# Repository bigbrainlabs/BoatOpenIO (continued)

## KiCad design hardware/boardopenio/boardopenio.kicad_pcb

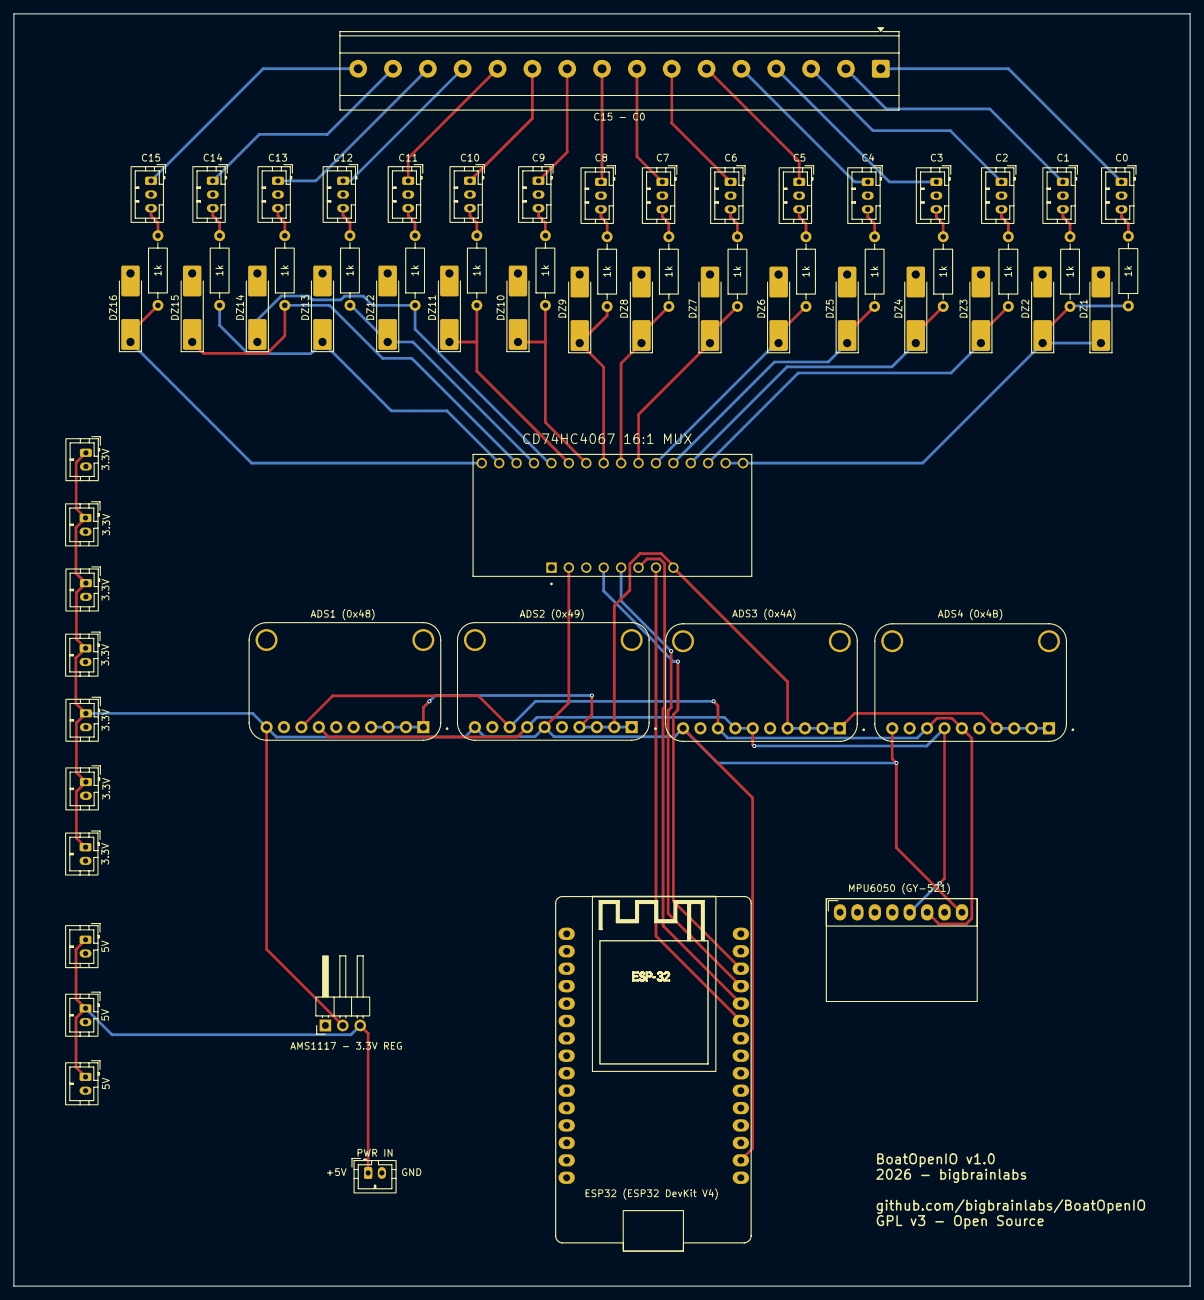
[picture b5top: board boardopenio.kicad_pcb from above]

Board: 2 copper layers, 171.5 x 185.5 mm, 68 parts (0 on the bottom side), 57 nets.

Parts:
3.3V, 3.3V#2, 3.3V#3, 3.3V#4, 3.3V#5, 3.3V#6, 3.3V#7, 5V, 5V#2, 5V#3: Conn_01x02; JST_PH_B2B-PH-K_1x02_P2.00mm_Vertical
ADS1 (0x48), ADS2 (0x49), ADS3 (0x4A), ADS4 (0x4B): ZC261500; MODULE_ZC261500
AMS1117 - 3.3V REG: AMS1117CD-3.3; PinHeader_1x03_P2.54mm_Horizontal
C0, C1, C2, C3, C4, C5, C6, C7, C8, C9, C10, C11, C12, C13, C14, C15: Conn_01x03_Pin; JST_PH_B3B-PH-K_1x03_P2.00mm_Vertical
C15 - C0: Screw_Terminal_01x16; TerminalBlock_Phoenix_MKDS-3-16-5.08_1x16_P5.08mm_Horizontal
CD74HC4067 16:1 MUX: CD74HC4067 MUX; MODULE_BOB-09056
DZ1, DZ2, DZ3, DZ4, DZ5, DZ6, DZ7, DZ8, DZ9, DZ10, DZ11, DZ12, DZ13, DZ14, DZ15, DZ16: Zener 3v3; D_MELF-RM10_Universal_Handsoldering
ESP32 (ESP32 DevKit V4): DOIT_ESP32_DEVKIT_30Pins
MPU6050 (GY-521): MPU6050; MPU6050_Breakout
PWR IN: Conn_01x02; JST_PH_B2B-PH-K_1x02_P2.00mm_Vertical
R1, R2, R3, R4, R5, R6, R7, R8, R9, R10, R11, R12, R13, R14, R15, R16: 1k; R_Axial_DIN0207_L6.3mm_D2.5mm_P10.16mm_Horizontal

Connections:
GND: 3.3V.2, 3.3V#2.2, 3.3V#3.2, 3.3V#4.2, 3.3V#5.2, 3.3V#6.2, 3.3V#7.2, 5V.2, 5V#2.2, 5V#3.2, ADS1 (0x48).6 (ADDR), ADS1 (0x48).9 (GND), ADS2 (0x49).9 (GND), ADS3 (0x4A).9 (GND), ADS4 (0x4B).9 (GND), AMS1117 - 3.3V REG.1 (GND), C0.2, C1.2, C2.2, C3.2, C4.2, C5.2, C6.2, C7.2, C8.2, C9.2, C10.2, C11.2, C12.2, C13.2, C14.2, C15.2, CD74HC4067 16:1 MUX.JP3-1 (GND), CD74HC4067 16:1 MUX.JP3-3 (EN), DZ1.2 (A), DZ2.2 (A), DZ3.2 (A), DZ4.2 (A), DZ5.2 (A), DZ6.2 (A), DZ7.2 (A), DZ8.2 (A), DZ9.2 (A), DZ10.2 (A), DZ11.2 (A), DZ12.2 (A), DZ13.2 (A), DZ14.2 (A), DZ15.2 (A), DZ16.2 (A), ESP32 (ESP32 DevKit V4).1 (GND), ESP32 (ESP32 DevKit V4).15 (GND), MPU6050 (GY-521).7 (GND), PWR IN.2
unnamed: CD74HC4067 16:1 MUX.JP1-15 (C14), CD74HC4067 16:1 MUX.JP1-16 (C15), DZ1.1 (K), DZ2.1 (K), R1.1, R2.1
unnamed: CD74HC4067 16:1 MUX.JP1-14 (C13), DZ3.1 (K), R3.1
unnamed: CD74HC4067 16:1 MUX.JP1-13 (C12), DZ4.1 (K), R4.1
unnamed: CD74HC4067 16:1 MUX.JP1-12 (C11), DZ5.1 (K), R5.1
unnamed: CD74HC4067 16:1 MUX.JP1-11 (C10), DZ6.1 (K), R6.1
unnamed: CD74HC4067 16:1 MUX.JP1-10 (C9), DZ7.1 (K), R7.1
unnamed: CD74HC4067 16:1 MUX.JP1-9 (C8), DZ8.1 (K), R8.1
unnamed: CD74HC4067 16:1 MUX.JP1-8 (C7), DZ9.1 (K), R9.1
unnamed: CD74HC4067 16:1 MUX.JP1-7 (C6), DZ10.1 (K), R10.1
unnamed: CD74HC4067 16:1 MUX.JP1-6 (C5), DZ11.1 (K), R11.1
unnamed: CD74HC4067 16:1 MUX.JP1-4 (C3), DZ12.1 (K), R13.1
unnamed: CD74HC4067 16:1 MUX.JP1-2 (C1), DZ13.1 (K), R15.1
unnamed: CD74HC4067 16:1 MUX.JP1-5 (C4), DZ14.1 (K), R12.1
unnamed: CD74HC4067 16:1 MUX.JP1-3 (C2), DZ15.1 (K), R14.1
unnamed: CD74HC4067 16:1 MUX.JP1-1 (C0), DZ16.1 (K), R16.1
unnamed: C0.1, C15 - C0.1
unnamed: C0.3, R1.2
unnamed: C1.1, C15 - C0.2
unnamed: C1.3, R2.2
unnamed: C2.3, R3.2
unnamed: C3.3, R4.2
unnamed: C4.3, R5.2
unnamed: C5.3, R6.2
unnamed: C6.3, R7.2
unnamed: C7.3, R8.2
unnamed: C8.3, R9.2
unnamed: C9.1, C15 - C0.10
unnamed: C9.3, R10.2
unnamed: C10.1, C15 - C0.11
unnamed: C10.3, R11.2
unnamed: C11.1, C15 - C0.12
unnamed: C11.3, R12.2
unnamed: C12.1, C15 - C0.13
unnamed: C12.3, R13.2
unnamed: C13.1, C15 - C0.14
unnamed: C13.3, R14.2
unnamed: C14.1, C15 - C0.15
unnamed: C14.3, R15.2
unnamed: C15.1, C15 - C0.16
unnamed: C15.3, R16.2
unnamed: 3.3V.1, 3.3V#2.1, 3.3V#3.1, 3.3V#4.1, 3.3V#5.1, 3.3V#6.1, 3.3V#7.1, ADS1 (0x48).10 (VDD), ADS2 (0x49).6 (ADDR), ADS2 (0x49).10 (VDD), ADS3 (0x4A).10 (VDD), ADS4 (0x4B).10 (VDD), AMS1117 - 3.3V REG.2 (VO), CD74HC4067 16:1 MUX.JP3-2 (VCC), ESP32 (ESP32 DevKit V4).2 (VDD), MPU6050 (GY-521).8 (VCC)
unnamed: 5V.1, 5V#2.1, 5V#3.1, AMS1117 - 3.3V REG.3 (VI), PWR IN.1
unnamed: C2.1, C15 - C0.3
unnamed: C3.1, C15 - C0.4
unnamed: C4.1, C15 - C0.5
unnamed: C5.1, C15 - C0.6
unnamed: C6.1, C15 - C0.7
unnamed: C7.1, C15 - C0.8
unnamed: C8.1, C15 - C0.9
unnamed: CD74HC4067 16:1 MUX.JP3-4 (S0), ESP32 (ESP32 DevKit V4).13 (IO14)
unnamed: ADS1 (0x48).7 (SDA), ADS2 (0x49).7 (SDA), ADS3 (0x4A).6 (ADDR), ADS3 (0x4A).7 (SDA), ADS4 (0x4B).7 (SDA), MPU6050 (GY-521).5 (SDA)
unnamed: ADS1 (0x48).8 (SCL), ADS2 (0x49).8 (SCL), ADS3 (0x4A).8 (SCL), ADS4 (0x4B).6 (ADDR), ADS4 (0x4B).8 (SCL), MPU6050 (GY-521).6 (SCL)
unnamed: CD74HC4067 16:1 MUX.JP3-7 (S3), ESP32 (ESP32 DevKit V4).10 (IO25)
unnamed: CD74HC4067 16:1 MUX.JP3-6 (S2), ESP32 (ESP32 DevKit V4).11 (IO26)
unnamed: CD74HC4067 16:1 MUX.JP3-5 (S1), ESP32 (ESP32 DevKit V4).12 (IO27)
unnamed: ADS1 (0x48).1 (A3), ADS1 (0x48).2 (A2), ADS1 (0x48).3 (A1), ADS1 (0x48).4 (A0), ADS2 (0x49).1 (A3), ADS2 (0x49).2 (A2), ADS2 (0x49).3 (A1), ADS2 (0x49).4 (A0), ADS3 (0x4A).1 (A3), ADS3 (0x4A).2 (A2), ADS3 (0x4A).3 (A1), ADS3 (0x4A).4 (A0), ADS4 (0x4B).1 (A3), ADS4 (0x4B).2 (A2), ADS4 (0x4B).3 (A1), ADS4 (0x4B).4 (A0), CD74HC4067 16:1 MUX.JP3-8 (COM)

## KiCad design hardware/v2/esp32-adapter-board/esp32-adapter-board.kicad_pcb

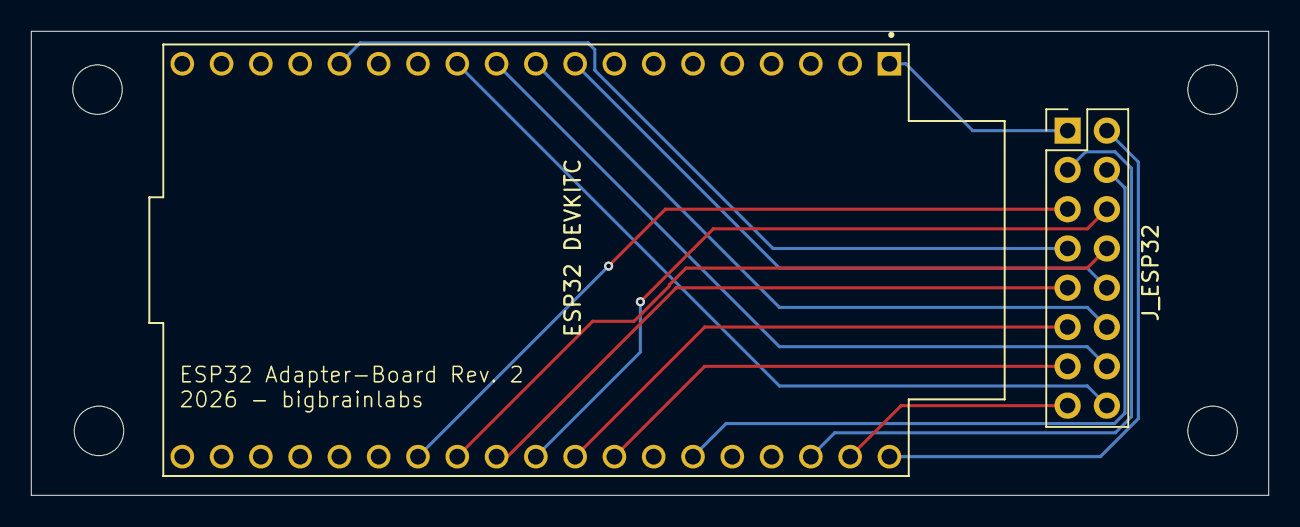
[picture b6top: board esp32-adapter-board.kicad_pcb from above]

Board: 2 copper layers, 80.0 x 30.0 mm, 6 parts (0 on the bottom side), 16 nets.

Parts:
B1, B2, B3, B4: MountingHole_3.2mm_M3
ESP32 DEVKITC: ESP32-WROOM-32D; MODULE_ESP32-DEVKITC
J_ESP32: Conn_02x08_Odd_Even; PinHeader_2x08_P2.54mm_Vertical

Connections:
unnamed: ESP32 DEVKITC.1 (3V3), J_ESP32.1
unnamed: ESP32 DEVKITC.38 (GND3), J_ESP32.2
unnamed: ESP32 DEVKITC.36 (IO22), J_ESP32.3
unnamed: ESP32 DEVKITC.33 (IO21), J_ESP32.4
unnamed: ESP32 DEVKITC.26 (IO4), J_ESP32.5
unnamed: ESP32 DEVKITC.29 (IO5), J_ESP32.6
unnamed: ESP32 DEVKITC.15 (IO13), J_ESP32.7
unnamed: ESP32 DEVKITC.27 (IO16), J_ESP32.8
unnamed: ESP32 DEVKITC.28 (IO17), J_ESP32.9
unnamed: ESP32 DEVKITC.9 (IO25), J_ESP32.10
unnamed: ESP32 DEVKITC.30 (IO18), J_ESP32.11
unnamed: ESP32 DEVKITC.10 (IO26), J_ESP32.12
unnamed: ESP32 DEVKITC.31 (IO19), J_ESP32.13
unnamed: ESP32 DEVKITC.11 (IO27), J_ESP32.14
unnamed: ESP32 DEVKITC.37 (IO23), J_ESP32.15
unnamed: ESP32 DEVKITC.12 (IO14), J_ESP32.16

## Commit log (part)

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2026-05-19 Initial commit: README und Architekturschema
    README mit Projektbeschreibung und erste SVG-Schemazeichnung der Systemarchitektur.
2026-06-16 Add files via upload
    ready v1 pcb - failed
